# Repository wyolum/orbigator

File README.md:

# 🌍 Orbigator: The Analog Orbit Propagator

> "What hardware hacker doesn’t have a soft spot for transparent cases? ... [wyojustin] has done a fantastic job of documenting the hardware and software aspects of the build." — **[Hackaday](https://hackaday.com/2026/03/08/the-orbigator-satellite-tracking-with-style/)** ([Full Feature Archive](docs/HACKADAY_FEATURE.md))

**The Orbigator** is an open-source, physical satellite tracker that turns complex orbital mechanics into a desk-side companion. Powered by the **Raspberry Pi Pico 2** and precision **DYNAMIXEL servos**, it physically points to the ISS (or any satellite) in real-time with zero drift.

---

## 🚀 Why the Orbigator?

Inspired by [Will’s Builds ISS tracker](https://hackaday.com/2025/07/08/touch-lamp-tracks-iss-with-style/), the Orbigator introduces several key technical innovations to the DIY tracker space:

### 🔄 Continuous, Uninterrupted Motion
Unlike traditional trackers that use static globes (requiring wire unwinding every orbit), the Orbigator features a **rotating globe**. This allows for smooth, continuous tracking across multiple revolutions without ever needing to reset or "unwind."

### 🎯 LVLH Attitude Control
The orbital mechanics are implemented directly in the hardware geometry (inclination angle). This ensures the satellite pointer maintains a true **LVLH (Local Vertical, Local Horizontal)** attitude throughout the entire pass—exactly how real satellites orient themselves.

### 🧩 Zero-Drift absolute Positioning
Leveraging the 32-bit absolute resolvers in DYNAMIXEL XL330-M288-T motors, the system recovers its orientation instantly after power cycles. No homing, no limits, and no drift—just persistent, mathematical accuracy.

---

## 🛠️ Technical Deep Dive

*Complete Mechanical Assembly: Precision motion and integrated control.*

### Lightweight, High-Performance Propagator
The heart of the Orbigator is a custom, **lightweight SGP4 implementation** running natively on the Pico 2's RISC-V cores. Eschewing heavy ports, it was rolled specifically to provide mathematical accuracy within the visual tolerances of the physical hardware, handling real-time TLE propagation and J2 perturbation effects entirely in MicroPython.

### Split-Screen Radar UI
A custom **SH1106 OLED driver** provides a powerful command center:
*   **Live Radar Plot**: A dynamic "Sky Plot" of the current satellite pass.
*   **Localized World Map**: High-speed bitmask rendering provides a 90° ground track view centered on your observer location.

### Smart Persistence
The system monitors its own state and saves to Flash/SRAM only during ideal intervals (e.g., at equator crossings) to maximize flash lifespan while ensuring a perfect "instant-on" recovery.

---

## 📦 Repository Structure

| Path | Description |
|------|-------------|
| [**micropython/**](micropython/) | Firmware: SGP4 propagator, UI stacks, and motor drivers. |
| [**fabricate/**](fabricate/) | Mechanical design: OpenSCAD files for 3D printing and assembly. |
| [**kicad/**](kicad/) | Electronics: PCB designs and schematics. |
| [**web/**](micropython/web/) | Dashboard: Real-time control and configuration via web interface. |

---

## ⚡ Quick Start

1.  **3D Print**: High-quality production STLs are located in [**fabricate/stls/Production/**](fabricate/stls/Production/).
2.  **Assemble**: Follow our step-by-step [**Assembly Instructions**](docs/ASSEMBLY.md).
3.  **Flash MicroPython**: Install the Pico 2 firmware.
4.  **Upload Code**: Use Thonny or `mpremote` to copy the `micropython/` files to the board.
5.  **Track!**: Power up and select your satellite from the "SGP4" menu.

---

## 🧾 Bill of Materials (BOM)

### Electronics
*   **Controller**: [Raspberry Pi Pico 2W](https://www.adafruit.com/product/6087)
*   **Motors**: 2x [DYNAMIXEL XL330-M288-T](https://robotis.us/dynamixel-xl330-m288-t/)
*   **Display/UI**: [I2C OLED Display with EC11 Rotary Encoder](https://www.crcibernetica.com/i2c-oled-display-with-ec11-rotary-encoder/) (includes 2x buttons)
*   **RTC**: [DS3232 Precision RTC](https://www.dfrobot.com/product-2304.html)
*   **Logic**: 1x [SN74HC126N Quad Tri-State Buffer](https://www.digikey.com/en/products/detail/texas-instruments/SN74HC126N/376889) (for half-duplex UART)
*   **Passives**: 1x 10kΩ resistor, 2x 4.7kΩ resistors
*   **Power**: 5V 4-5A External Power Supply with [5.5mm DC Barrel Jack](https://www.amazon.com/dp/B0D9B7WR23)

### Hardware & Mechanical
*   **Globe**: [12" Transparent Desktop Globe](https://www.amazon.com/dp/B0086OHL9A)
*   **Bearings**: 3x [13mm OD Carbon Steel Ball Bearings](https://www.amazon.com/dp/B07SV6QSR3) (e.g., 624ZZ) and [High-Performance Skate Bearings](https://www.amazon.com/dp/B09MPMW1XQ)
*   **Fasteners**: Self-tapping screws (included with motors), [M3 Male Stud Mounting Magnets](https://www.kjmagnetics.com/mm-c-12-neodymium-male-stud-mounting-magnet?pl=1.2&pf=), and [Tension Springs](https://www.amazon.com/dp/B076LZ8L1M)
*   **Hardware**: 10-20 US pennies (used as counterweight)
*   **3D Parts**: Printed from the `Production/` folder (PLA or PETG)

---

## 📐 3D Printing (Production Parts)

The following parts are required for the full assembly and can be found in `fabricate/stls/Production/`. **The leading number in the filename indicates the required print quantity.**

*   `1_drive_gear.stl` - Main EQX drive
*   `1_flex_aov_arm.stl` - Satellite pointer arm
*   `1_globe_interface.stl` - Secure mount for the globe
*   `1_inclination_aov_mount.stl` - Hardware-implemented inclination bracket
*   `1_sled_3.stl` - Electronic housing and base
*   `1_full_assembly.stl` - Reference model (not for printing)
*   `3_swingarm.stl` - Differential assembly components
*   `3_shim.stl` - Insert for the skate bearings (see `misc.scad` for 13mm dims)
*   `3_washer.stl` - Vertical stop for the ring gear

---

## 📸 Media: As Seen on [WyoLum Blog](https://wyolum.com/orbigator-real-time-satellite-tracker-with-overhead-alert-radar/)

| [**Earthrise Shot**](docs/images/orbigator_lunar_display.jpg) | [**World Map Tracking**](docs/images/orbigator_worldmap_tracking.png) |
|:---:|:---:|
|  |  |
| *ISS Tracking with Lunar Projection.* | *Real-time World Map Context.* |

### System Details
| UI & Setup | Electronics | Mechanical Assembly | Technical Render |
|:---:|:---:|:---:|:---:|
|  |  |  |  |
| *Real-time status* | *Pico 2 & Buffers* | *Internal Hardware* | *Mathematical precision* |

> "A beautiful mix of technical precision and mechanical elegance."

---

## ⚖️ License

Distributed under the MIT License.

---

**Developed with ❤️ by wyojustin**
[GitHub](https://github.com/wyolum/orbigator)

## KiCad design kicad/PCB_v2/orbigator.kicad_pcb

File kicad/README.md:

# Orbigator KiCad Project

This directory contains the KiCad PCB design files for the Orbigator orbital mechanics simulator.

## Project Structure

```
kicad/
├── orbigator.kicad_pro      # KiCad 8.x project file
├── orbigator.kicad_sch      # Main schematic file
├── orbigator.kicad_pcb      # PCB layout file
├── sym-lib-table            # Symbol library table
├── fp-lib-table             # Footprint library table
├── orbigator.pretty/        # Custom footprints
├── bom/                     # Bill of Materials exports
├── gerber/                  # Gerber files for manufacturing
├── pdf/                     # PDF exports of schematics
├── renders/                 # PCB renders
├── 3D_models/               # Custom 3D models
└── orbigator-backups/       # Automatic backups
```

## Quick Start

1. Open `orbigator.kicad_pro` in KiCad 8.x
2. Review the schematic in the Schematic Editor
3. Use the reference documentation in the parent directory:
   - `ORBIGATOR_CIRCUIT_DIAGRAM.txt` - ASCII circuit diagram
   - `ORBIGATOR_PIN_ASSIGNMENTS.txt` - Pin assignments
   - `NOTE_FOR_ANOOL_I2C_PULLUPS.txt` - Critical design notes
   - `BOM.md` - Detailed component specifications

## Key Design Requirements

### Critical Components
- **I2C Pull-ups**: 4.7kΩ resistors on SDA and SCL (REQUIRED for multi-device bus)
- **RTC Backup**: 0.47F supercapacitor with 47Ω charging resistor (recommended)
- **DATA Bus Pull-up**: 10kΩ resistor to +5V for DYNAMIXEL communication

> **Note for Anool**: For the RTC (DS3231), you can choose between:
> 1. Using a ChronoDot module breakout (simple pinout connection)
> 2. Integrating the DS3231 chip directly with battery backup (CR2032)
> 3. Integrating the DS3231 chip directly with supercapacitor backup (0.47F)
> 
> The choice is yours based on board space, cost, and maintenance preferences.

### Power Requirements
- **3.3V Rail**: Pico 2, 74HC126, OLED, RTC (low current)
- **5V Rail**: DYNAMIXEL motors (4-5A external supply required)

### Connectors
- **DYNAMIXEL**: 3-pin JST connectors (daisy-chained)
- **Encoder**: 5-pin header (A, B, SW, VCC, GND)
- **Power**: Barrel jack or terminal block for 5V input

## Design Notes

This PCB is designed to be a single-board controller for the Orbigator display.
All components should be easily hand-solderable (through-hole or large SMD).

The design prioritizes:
- Reliability (proper pull-ups, decoupling)
- Serviceability (labeled connectors, test points)
- Compactness (suitable for display base mounting)

## Manufacturing

Standard 2-layer PCB:
- Thickness: 1.6mm
- Copper: 1oz
- Finish: HASL or ENIG
- Minimum trace: 0.2mm
- Minimum clearance: 0.2mm

## Author

Design by Anool Mahidharia (WyoLum)
Based on specifications by Justin Shaw

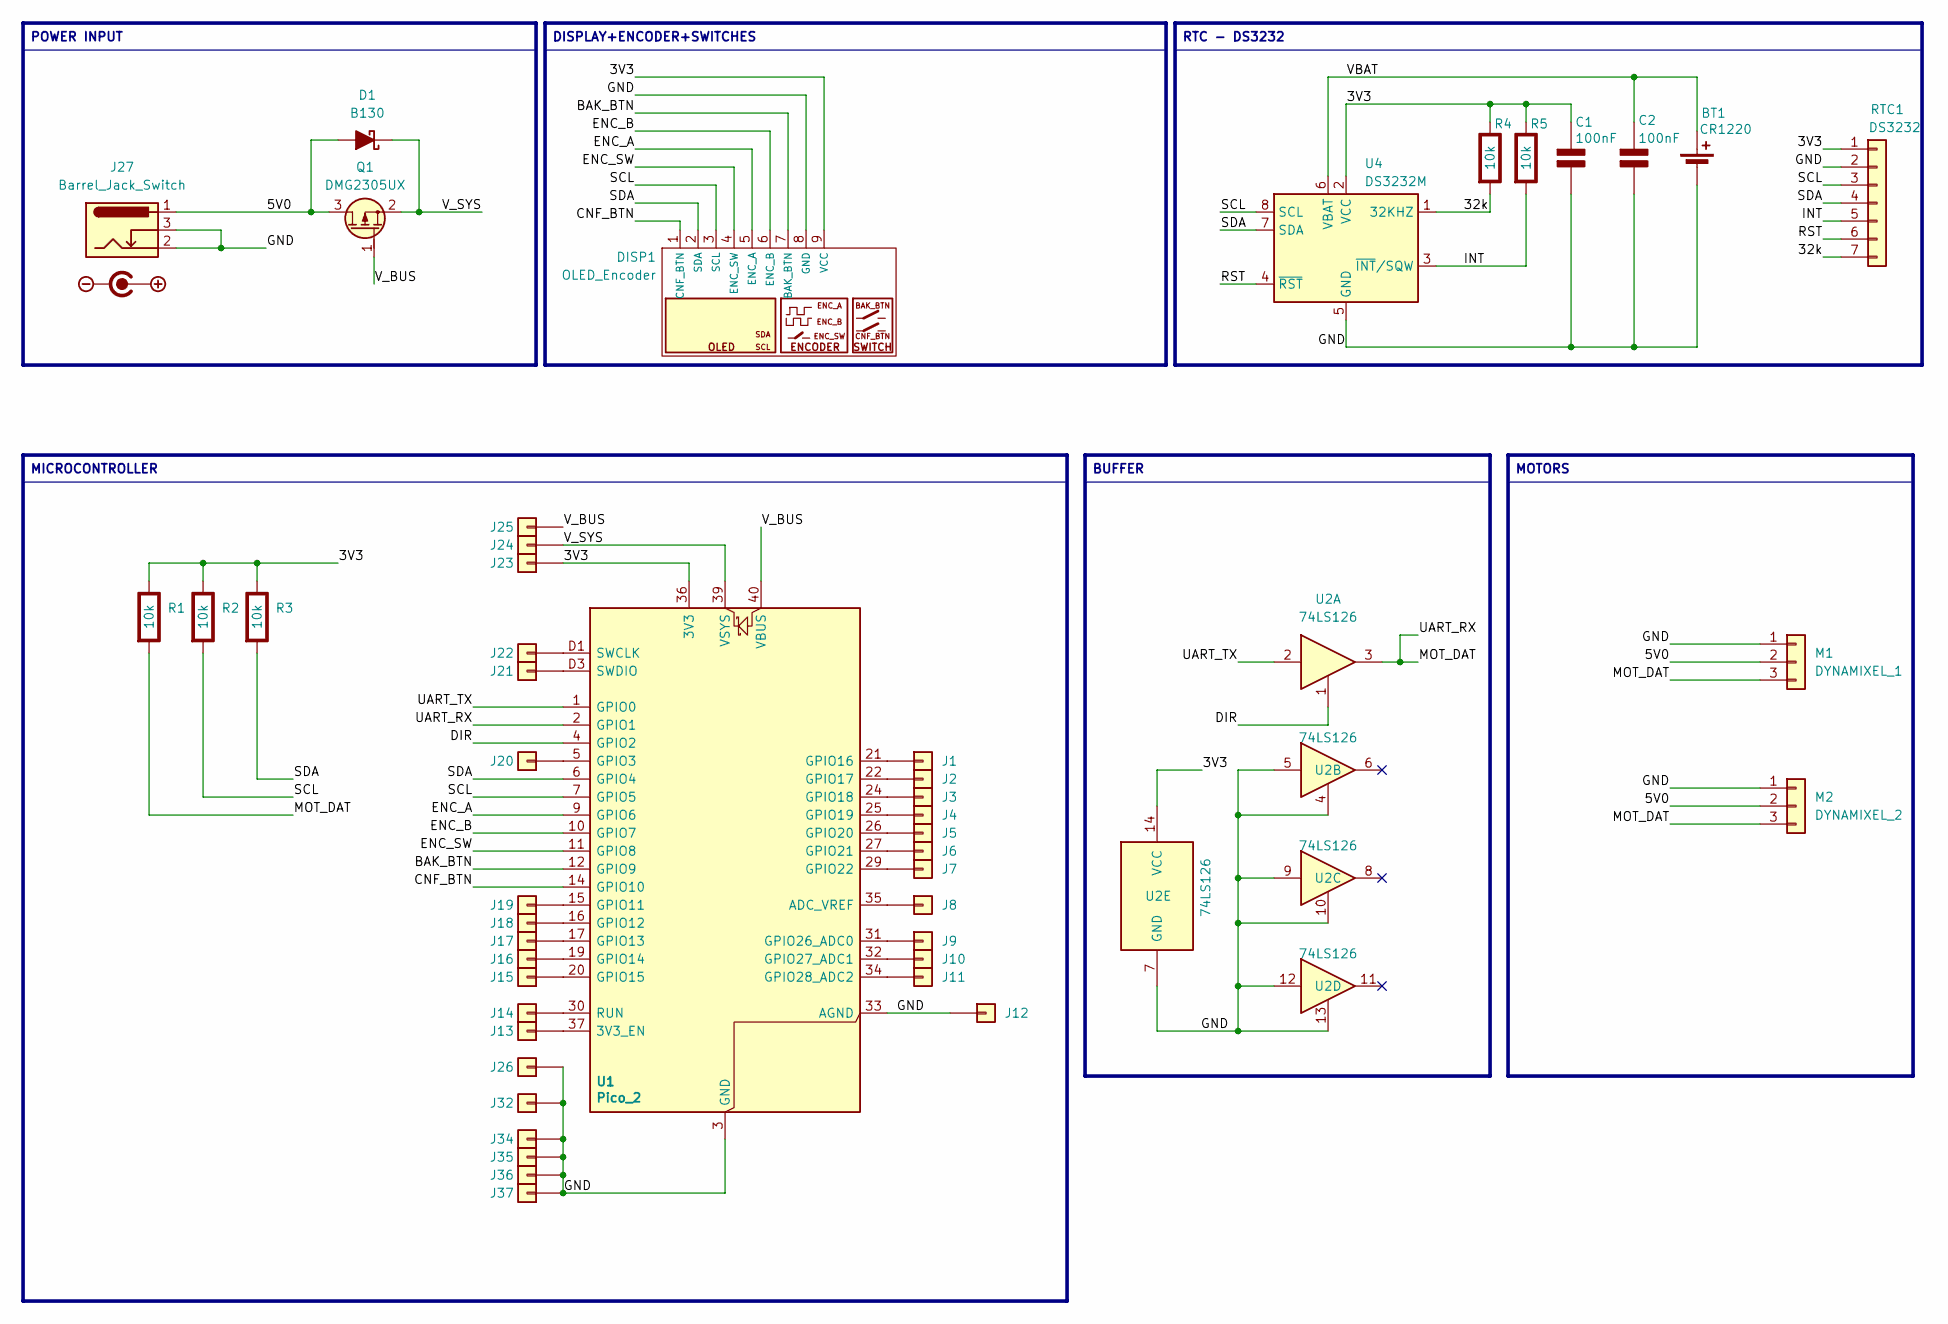
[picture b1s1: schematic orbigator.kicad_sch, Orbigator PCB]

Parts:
BT1: CR1220; BatteryHolder_LINX_BAT-HLD-012-SMT
C1, C2: 100nF; C_0805_2012Metric_Pad1.18x1.45mm_HandSolder; Rating V
D1: B130; D_SMA
DISP1: OLED_Encoder; OLED_ENC3
J1, J2, J3, J4, J5, J6, J7, J8, J9, J10, J11, J12, J13, J14, J15, J16, J17, J18, J19, J20, J21, J22, J23, J24, J25, J26, J32, J34, J35, J36, J37: Conn_01x01; PinHeader_1x01_P2.54mm_Vertical
J27: Barrel_Jack_Switch; BarrelJack_Horizontal
M1: DYNAMIXEL_1; JST_EH_B3B-EH-A_1x03_P2.50mm_Vertical
M2: DYNAMIXEL_2; JST_EH_B3B-EH-A_1x03_P2.50mm_Vertical
Q1: DMG2305UX; SOT-23
R1, R2, R3, R4, R5: 10k; R_0805_2012Metric_Pad1.20x1.40mm_HandSolder; Rating W
RTC1: DS3232; DS3232_RTC_vert
U1: Pico_2; RaspberryPi_Pico_SMD_HandSolder
U2: 74LS126; SOIC-14_3.9x8.7mm_P1.27mm
U3: DC_polarity; DC
U4: DS3232M; SOIC-8_3.9x4.9mm_P1.27mm

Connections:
/3V3: C1.1 (+), DISP1.9 (VCC), J23.1, R1.1 (+), R2.1 (+), R3.1 (+), R4.1 (+), R5.1 (+), RTC1.1, U1.36 (3V3), U2.14 (VCC), U4.2 (VCC)
/5V0: D1.2 (A), J27.1, M1.2, M2.2, Q1.3 (D)
/32k: R4.2 (-), RTC1.7, U4.1 (32KHZ)
/BAK_BTN: DISP1.7 (BAK_BTN), U1.12 (GPIO9)
/CNF_BTN: DISP1.1 (CNF_BTN), U1.14 (GPIO10)
/DIR: U1.4 (GPIO2), U2.1
/ENC_A: DISP1.5 (ENC_A), U1.9 (GPIO6)
/ENC_B: DISP1.6 (ENC_B), U1.10 (GPIO7)
/ENC_SW: DISP1.4 (ENC_SW), U1.11 (GPIO8)
/GND: BT1.2 (-), C1.2 (-), C2.2 (-), DISP1.8 (GND), J12.1, J26.1, J27.2, J27.3, J32.1, J34.1, J35.1, J36.1, J37.1, M1.1, M2.1, RTC1.2, U1.3 (GND), U1.8 (GND), U1.13 (GND), U1.18 (GND), U1.23 (GND), U1.28 (GND), U1.33 (AGND), U1.38 (GND), U1.D2 (GND), U2.4, U2.5, U2.7 (GND), U2.9, U2.10, U2.12, U2.13, U4.5 (GND)
/INT: R5.2 (-), RTC1.5, U4.3 (~INT/SQW)
/MOT_DAT: M1.3, M2.3, R1.2 (-), U1.2 (GPIO1), U2.3
/RST: RTC1.6, U4.4 (~RST)
/SCL: DISP1.3 (SCL), R2.2 (-), RTC1.3, U1.7 (GPIO5), U4.8 (SCL)
/SDA: DISP1.2 (SDA), R3.2 (-), RTC1.4, U1.6 (GPIO4), U4.7 (SDA)
/UART_TX: U1.1 (GPIO0), U2.2
/VBAT: BT1.1 (+), C2.1 (+), U4.6 (VBAT)
/V_BUS: J25.1, Q1.1 (G), U1.40 (VBUS)
/V_SYS: D1.1 (K), J24.1, Q1.2 (S), U1.39 (VSYS)
unnamed: J1.1, U1.21 (GPIO16)
unnamed: J2.1, U1.22 (GPIO17)
unnamed: J3.1, U1.24 (GPIO18)
unnamed: J4.1, U1.25 (GPIO19)
unnamed: J5.1, U1.26 (GPIO20)
unnamed: J6.1, U1.27 (GPIO21)
unnamed: J7.1, U1.29 (GPIO22)
unnamed: J8.1, U1.35 (ADC_VREF)
unnamed: J9.1, U1.31 (GPIO26_ADC0)
unnamed: J10.1, U1.32 (GPIO27_ADC1)
unnamed: J11.1, U1.34 (GPIO28_ADC2)
unnamed: J13.1, U1.37 (3V3_EN)
unnamed: J14.1, U1.30 (RUN)
unnamed: J15.1, U1.20 (GPIO15)
unnamed: J16.1, U1.19 (GPIO14)
unnamed: J17.1, U1.17 (GPIO13)
unnamed: J18.1, U1.16 (GPIO12)
unnamed: J19.1, U1.15 (GPIO11)
unnamed: J20.1, U1.5 (GPIO3)
unnamed: J21.1, U1.D3 (SWDIO)
unnamed: J22.1, U1.D1 (SWCLK)

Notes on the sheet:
DISPLAY+ENCODER+SWITCHES
POWER INPUT
MOTORS
RTC - DS3232
BUFFER
MICROCONTROLLER

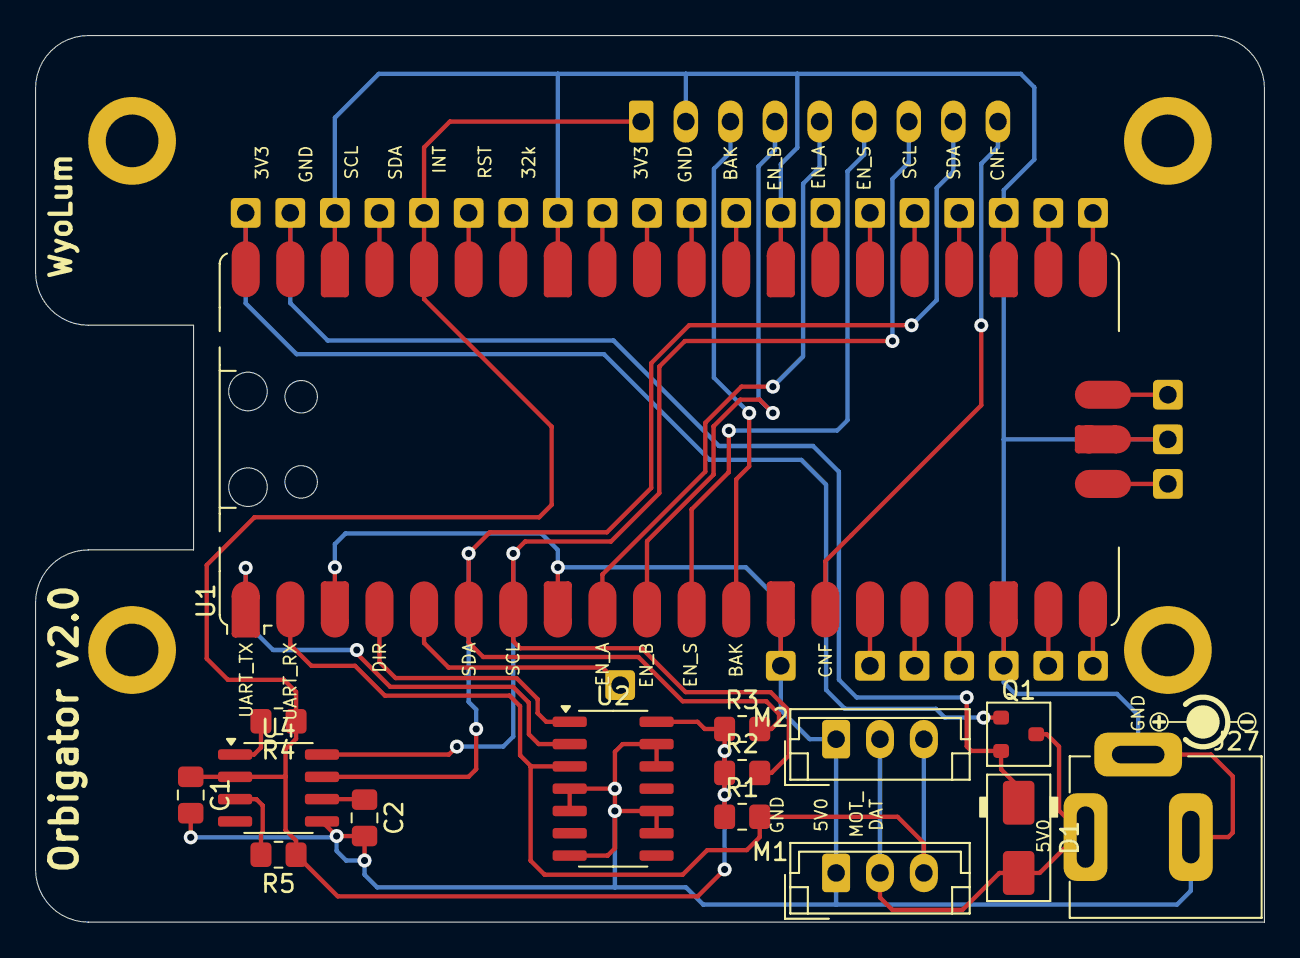
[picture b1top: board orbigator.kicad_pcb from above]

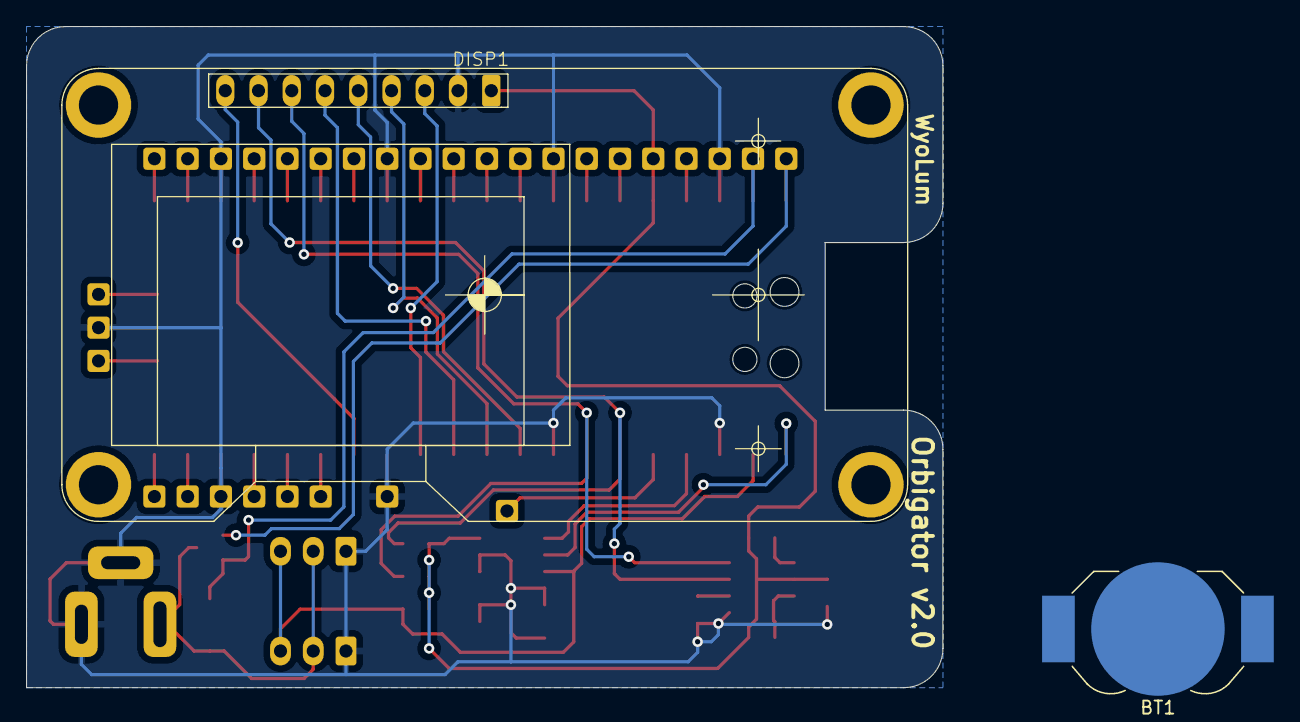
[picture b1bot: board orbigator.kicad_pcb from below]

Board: 2 copper layers, 70.0 x 50.5 mm, 49 parts (2 on the bottom side), 39 nets.

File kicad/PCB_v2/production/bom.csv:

Designator,Footprint,Quantity,Value,LCSC Part #,JLCPCB Part #,LINK
BT1,BatteryHolder_LINX_BAT-HLD-012-SMT,1,CR1220,C381116,,
"C1, C2",805,2,100nF,C49678,,https://www.lcsc.com/product-detail/C49678.html?s_z=n_CC0805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
D1,D_SMA,1,B130,C134423,,https://www.lcsc.com/product-detail/C134423.html?s_z=n_B130-13-F
DISP1,OLED_ENC3,1,OLED_Encoder,,,
J27,BarrelJack_Horizontal,1,Barrel_Jack_Switch,C381116,,https://www.lcsc.com/product-detail/C381116.html
M1,JST_EH_B3B-EH-A_1x03_P2.50mm_Vertical,1,DYNAMIXEL_1,C160259,,https://www.lcsc.com/product-detail/C160259.html?s_z=n_JST_E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
M2,JST_EH_B3B-EH-A_1x03_P2.50mm_Vertical,1,DYNAMIXEL_2,C160259,,https://www.lcsc.com/product-detail/C160259.html?s_z=n_JST_E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
Q1,SOT-23,1,DMG2305UX,C150470,,https://www.lcsc.com/product-detail/C150470.html?s_z=n_DMG2305UX
"R1, R2, R3, R4, R5",805,5,10k,C84376,,https://www.lcsc.com/product-detail/C84376.html
U1,RaspberryPi_Pico_SMD_HandSolder,1,Pico_2,,C41407547,https://jlcpcb.com/partdetail/RaspberryPi-Pico2/C41407547
U2,SOIC-14_3.9x8.7mm_P1.27mm,1,74LS126,C7644,,https://www.lcsc.com/product-detail/C7644.html?s_z=n_SN74HC126DR
U4,SOIC-8_3.9x4.9mm_P1.27mm,1,DS3232M,C2827535,,https://www.lcsc.com/product-detail/C2827535.html?s_z=n_DS3232M

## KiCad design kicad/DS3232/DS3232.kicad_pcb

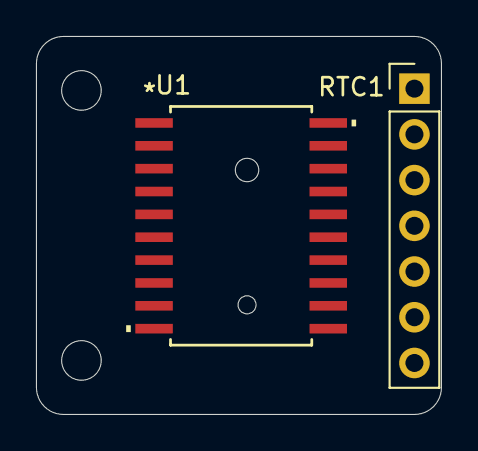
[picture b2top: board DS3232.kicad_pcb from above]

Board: 2 copper layers, 22.5 x 21.0 mm, 5 parts (1 on the bottom side), 7 nets, no tracks yet.

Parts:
BT1: CR1220; BAT_1056
H1, H2: MountingHole; MountingHole_2.2mm_M2
RTC1: DS3232; PinHeader_1x07_P2.54mm_Vertical
U1: ds3232sn-; 21-0042B_20_MXM-M

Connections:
/3V3: RTC1.1, U1.4 (VCC)
/32k: RTC1.7, U1.3 (32KHZ)
/GND: RTC1.2, U1.15 (GND)
/INT: RTC1.5, U1.5 (*INT/SQW)
/RST: RTC1.6, U1.6 (*RST)
/SCL: RTC1.3, U1.18 (SCL), U1.20 (SCL)
/SDA: RTC1.4, U1.17 (SDA)

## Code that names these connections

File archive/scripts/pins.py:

# pins.py - Orbigator GPIO Assignment Module
# Raspberry Pi Pico 2 with DYNAMIXEL XL330-M288-T Motors
# Aligned with orbigator.py and ORBIGATOR_PIN_ASSIGNMENTS.txt

from machine import Pin

# ---------------------------
# DYNAMIXEL Communication (UART0 + 74HC126 Buffer)
# ---------------------------
UART_TX = 0      # GP0 - UART0 TX → 74HC126 Pin 2 (1A)
UART_RX = 1      # GP1 - UART0 RX → DYNAMIXEL DATA line
UART_DIR = 2     # GP2 - Direction Control → 74HC126 Pin 1 (1OE)

# ---------------------------
# I2C Bus (OLED + DS3231 RTC)
# ---------------------------
I2C_SDA = 4      # GP4 - I2C0 SDA (shared: OLED + RTC)
I2C_SCL = 5      # GP5 - I2C0 SCL (shared: OLED + RTC)

# ---------------------------
# Rotary Encoder
# ---------------------------
ENC_A = 6        # GP6 - Encoder Phase A (with internal pull-up)
ENC_B = 7        # GP7 - Encoder Phase B (with internal pull-up)
ENC_SW = 8       # GP8 - Encoder Switch (with internal pull-up)

# ---------------------------
# Helper Pin Constructors
# ---------------------------
# UART pins (managed by UART peripheral, typically not constructed manually)
uart_dir_pin = Pin(UART_DIR, Pin.OUT)

# I2C pins (managed by I2C peripheral)
# i2c_sda_pin = Pin(I2C_SDA, Pin.OUT, Pin.OPEN_DRAIN)
# i2c_scl_pin = Pin(I2C_SCL, Pin.OUT, Pin.OPEN_DRAIN)

# Encoder pins
enc_a_pin = Pin(ENC_A, Pin.IN, Pin.PULL_UP)
enc_b_pin = Pin(ENC_B, Pin.IN, Pin.PULL_UP)
enc_sw_pin = Pin(ENC_SW, Pin.IN, Pin.PULL_UP)

# ---------------------------
# Motor Configuration
# ---------------------------
# DYNAMIXEL Motor IDs
MOTOR_ID_AOV = 1  # Argument of Vehicle (direct drive)
MOTOR_ID_EQX = 2  # Equator crossing (11T → 120T gearing)

# Gear Ratios
EQX_GEAR_RATIO = 120.0 / 11.0  # Ring gear / Drive gear
AOV_GEAR_RATIO = 1.0            # Direct drive

# ---------------------------
# UART Configuration
# ---------------------------
UART_BAUD = 57600
UART_BITS = 8
UART_PARITY = None
UART_STOP = 1

# ---------------------------
# I2C Configuration
# ---------------------------
I2C_FREQ = 100_000  # 100 kHz for reliability with ChronoDot/DS3231

# I2C Addresses
OLED_ADDR = 0x3C    # OLED Display (SH1106/SSD1306)
RTC_ADDR = 0x68     # DS3231 RTC (ChronoDot)

# ---------------------------
# Encoder Configuration
# ---------------------------
DETENT_DIV = 2      # Encoder counts per detent (for responsiveness)
DEBOUNCE_MS = 200   # Button debounce time in milliseconds

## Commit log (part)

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2025-07-25 initial
2025-07-28 reshuffle
2025-07-28 added screenshots
2025-07-28 added README
2025-11-17 scad work
2025-11-23 Add FreeCAD script to batch convert STL files to STEP format
    Creates step_files/ directory and converts all STL files from
    fabricate/ and fabricate/stls/ to STEP format using FreeCAD's
    mesh-to-solid conversion.
2025-11-23 added a list of stls to skip
2025-11-23 Switch to environment variables for FreeCAD script args
    FreeCAD intercepts command line arguments before they reach the script,
    so use STL_MODE and STL_FILES environment variables instead.
2025-11-23 Simplify STL-to-STEP script to just use skip list
    Removed environment variable complexity - just converts all STL files
    except those in SKIP_LIST.
2025-11-23 Add launch script for STL-to-STEP conversion
2025-11-23 Update render_aov_arm with full assembly transformation
2025-11-23 Add in-situ rendering for all assembly components
    - render_in_situ.scad: Master file with all component transformations
    - render_all_in_situ.sh: Batch script to render all components
    - stls_in_situ/: Output directory for positioned STL files
    Components include: aov_arm, aov_motor_mount, sled, ring_gear,
    drive_gear, base_with_1010_hole, RingLock, idler, spring_arms, pico
2025-11-23 Update render_aov_arm to use 'use' instead of 'include'
2025-11-23 Add render file for base_with_1010_hole in assembly position
2025-11-23 Add render file for 1010 aluminum extrusion in assembly position
2025-11-23 added in_situ step files
2025-11-30 updated files
2025-11-30 Update AOV motor to move ~0.5 degrees per encoder click
    - Set AOV_STEPS_PER_DETENT to 6 half-steps (~0.527 degrees)
    - Keep LAN_STEPS_PER_DETENT at 1 step
    - Update display to show AOV position in degrees instead of revolutions
    - More intuitive feedback for the highly-geared AOV motor
2025-12-01 Fix DS3231 I2C communication reliability
    - Switch from readfrom_mem to write-then-read method (more reliable)
    - Lower I2C frequency to 100kHz for better ChronoDot compatibility
    - Update both datetime() and temperature() methods
    - Fixes EIO error when reading from DS3231 registers
2025-12-02 Add long press time setting with DS3231 RTC integration
    - Long press (1s) encoder button enters time-setting mode
    - Short press cycles through states or time fields
    - Encoder adjusts hour/minute/year/month/day fields
    - Blinking cursor shows active field
    - Saves to DS3231 RTC on long press exit
    - Lower I2C frequency to 100kHz for RTC compatibility
2025-12-02 fix: Use str() wrapper for RTC exception to avoid printing errors
2025-12-02 fix: Add missing import time to ds3231.py and clean up debug statements
    - ds3231.py was missing 'import time' causing NameError during RTC init
    - Removed debug print statements from orbigator.py RTC initialization
    - RTC now initializes correctly with ChronoDot/DS3231 hardware
2025-12-07 Add DYNAMIXEL documentation and setup files
2025-12-07 Update documentation for XC330-M288-T servo selection
    XL330-M288-T backordered until Q1 2026. Selected XC330-M288-T as
    upgraded alternative with:
    - Metal gears (vs plastic)
    - Upgraded bearings
    - 78% more torque
    - Immediate availability
2025-12-16 Add DYNAMIXEL dry lab setup guide with official pinout diagram
    - Comprehensive step-by-step setup guide for XL330 motors
    - Pin identification guide showing mirrored connectors
    - Official ROBOTIS pinout diagram
    - Screw depth safety calculations
    - Drive shaft adapter with named parameters
2025-12-18 Orbigator Dynamixel Rewrite - Complete Implementation
    Major Changes:
    - Rewrote orbigator.py to use DYNAMIXEL XL330-M288-T motors (745 lines, down from 800)
    - Created motor abstraction layer (dynamixel_motor.py) with gear ratio support
    - Motor ID assignments: ID 1 = AoV (direct), ID 2 = LAN (10.909:1 geared)
    - Removed all stepper motor code (~400 lines)
    - Simplified motion control (motors handle acceleration internally)
2025-12-20 Fix motor control and I2C issues, add documentation
    Major fixes:
    - Add I2C pull-up resistors (4.7kΩ on SDA/SCL) to fix display glitching
    - Implement get_new_pos() for Extended Position Mode wrapping
    - Fix motor rate initialization bug when starting in state 3
    - Fix catch-up mechanism to prevent extreme motor movements
    - Reduce display update to 1Hz for better I2C performance
2025-12-21 Add KiCad PCB outline with centered mounting holes
    - Created orbigator.kicad_pcb with 55x70mm board outline
    - Board rotated 90° and centered on A4 sheet
    - Added 4x M3 mounting holes matching display board pattern
    - Holes positioned at (75.5,134), (75.5,163), (134.5,134), (134.5,163)
    - Hole pattern centered on board to align with display board
    - Added silkscreen text: 'Orbigator v1.0' and 'WyoLum'
2025-12-25 Add back/confirm buttons (GP9/GP10) and fix EQX motor direction
    - Added GP9 (Back button) and GP10 (Confirm button) to pin assignments
    - Updated component list to include new buttons
    - Fixed EQX motor direction (negated rate) - sun now rises in east
    - Added test_buttons.py for button verification
    - All buttons tested and working
2025-12-25 Implement revolution-based persistence, shortest-path catch-up logic, and hardware safety limits. Update README.
2025-12-25 Update all READMEs to reflect final Dynamixel/Mode-based features including Zulu time and inclination control.
2025-12-25 Add links to key documentation files in README.
2025-12-25 Added DYNAMIXEL XL-330 connector specifications document.
2025-12-25 Fixed dead DigiKey links for JST-GH housings and crimp contacts.
2025-12-25 Corrected JST-GH PCB header links in documentation.
2025-12-25 Updated PCB header links with cleaner Mouser URLs.
2025-12-25 Added Zulu Time (Datetime) editor and boot-time RTC reset check to prompt for time if reset.
2025-12-25 Updated upload script to include modes.py, orb_globals.py, and orb_utils.py.
2025-12-25 Promoted manual motor alignment to the main menu and verified encoder inversion.
2025-12-25 Added pro-tip about perfect stock cable lengths.
2025-12-25 Fixed AoV drift by implementing high-resolution system time syncing and high-precision catch-up anchors.
2025-12-25 Fixed Orbit re-entry drift by anchoring catch-up to current motor position relative to elapsed time.
2025-12-25 Reverted AoV speed limit to 10.
2025-12-25 Refactor: Introduced pins.py and addressed code review feedback.
2025-12-25 Added fine/coarse adjustment toggle to MotorEditorMode (encoder press switches between 1.0 and 0.1 degree steps)
2025-12-25 Implemented robustness improvements: centralized encoder policy and DYNAMIXEL communication resilience with retry logic and degraded mode
2025-12-25 Implemented elliptical orbit support with Kepler's equation solver, variable velocity integration, and UI editors for eccentricity and periapsis
2025-12-25 Added Plan13 satellite propagator and TLE utilities (adapted from bkerler/sattracker), created thank you note for bkerler
2025-12-25 Updated Plan13 test with current ISS TLE (TLE parsing still WIP)
2025-12-25 Added distance variation comparison over one orbit - ISS range varies by 729km (7.8%) from observer location
2025-12-25 Updated Plan13 GHAA for 2025 but still has 9400km longitude error - Plan13 unsuitable, need SGP4
2025-12-26 Discovered and validated existing SGP4 implementation - ready for satellite tracking integration
2025-12-28 Optimize performance, implement live motor tuning, and add incremental sync scripts
2025-12-28 SRAM state: add version byte + checksum validation
2025-12-30 SRAM state: integrate boot logging
2025-12-30 Mechanical: increase globe_interface_ring scale to 1.02 for better fit
2025-12-30 UI: universal accelerated encoder for all parameter editors
2025-12-30 UI: graphical degree symbol for OLED
2025-12-30 Docs: update Status Report for ChatGPT sharing
2025-12-30 Docs: finalize motor longevity wording for ChatGPT sharing
2026-01-03 Enable motors on hardware: Force torque ON and increase speed limit
2026-01-03 Fix SGP4 mapping: EQX formula and 2-digit year handling
2026-01-03 docs: add blog update and images
2026-01-04 KiCad schematic WiP
2026-01-07 Fix Motor Speed, SRAM Persistence, TrackLLMode, and Repo Cleanup
2026-01-07 Update gores: Full width tabs
2026-01-10 simple iss model added
2026-01-11 PCB check parts placement
2026-01-12 PCB modified RTC layout
2026-01-17 PCB layout please verify
2026-01-31 v2 DISP_ENC flip corrected in PCB
2026-02-01 Clean up backup and temp files
2026-02-02 v2 Motor connectors flip 180 deg in PCB
2026-02-08 WIP: Save current state before TDD rewrite
2026-02-18 feat: Final Polish - TLE Updates, Homing Fix, Stiction Tuning, Splash Screen
    - TLE Updates: 12h cycle with background check
    - Homing: AoV -> 90° Zenith, Nearest Logic
    - Tuning: AoV PID P=1000/I=50 to fix stiction
    - UX: Splash Screen with countdown + sh1106 refactor
    - Safety: 5s boot delay
    - Refactor: Shared sh1106 driver
2026-02-22 feat: Overhead Alert Radar (feature/overhead-alert-radar)
    - observer_frame.py: ECEF station + trig-free dot_up + az_el_deg
    - overhead_watcher.py: hysteresis state machine (HORIZON_ON=0)
    - radar_display.py: sky plot with trail ring buffer, 128x64
    - propagate.py: expose last_ecef from MicroSGP4
    - orb_globals.py: observer_frame, overhead_watcher, radar_display vars
    - orb_utils.py: fetch_observer_location() via Wyolum endpoint
2026-02-23 fix: trail 1pt/min, 20-pt buffer (covers full pass to set)
2026-02-23 feat: radar right-half layout, fast-forward test
    - radar_display: radar on right half (CX=96 R=29), Az/El on left
    - test: scan real TLE for next pass, animate actual track
2026-02-25 fix: DS3231 → DS3232 in live docs
2026-02-28 added production STLs
2026-03-02 Implement manual Lat/Lon editor and refactor overhead alert init
2026-03-02 fix: LatLonEditorMode arm logic — inline imports, drop redundant input_utils import
    Importing from orbigator.py would re-execute all module-level init code
    (motors, WiFi, etc.). Inline the three observer imports directly instead.
    Also remove the redundant local `import input_utils` since it is already
    imported at the top of modes.py.
    https://claude.ai/code/session_014H7TD89FRnXuv4wc5PGTdz
2026-03-08 Update README with Hackaday highlight and technical differentiators
2026-03-08 Detail 3D print quantities and mechanical roles in README
2026-03-08 Highlight main blog photos in README
2026-03-08 Fix README gallery formatting
2026-03-08 Update BOM with purchase links
2026-03-08 Update BOM with DS3232 and buffer links
2026-03-09 Add Hackaday quote to README
2026-03-09 Remove fake Hackaday.io link and fix accidental backticks
2026-03-09 Archive Hackaday feature and add display encoder layout
2026-03-10 Restore BOM components and clarify UI button inclusion
2026-03-11 Simplify Hackaday feature archive: remove community discussion
2026-03-22 orbigator v2 pcb ready for fab
2026-03-24 feat: add JLCPCB-format BOM for PCB v2
    Based on BOM.md v2.0 (supercap/bypass caps removed, CR2032 battery used).
    Includes LCSC part numbers for sourceable components, sourcing notes for
    modules ordered separately (Pico 2, OLED, RTC, DYNAMIXEL), and flags the
    SOIC-14 substitute for the DIP-14 74HC126 per the V2 SMD migration checklist.
    https://claude.ai/code/session_014H7TD89FRnXuv4wc5PGTdz
2026-03-26 orbigator v2 WIP2 - not final yet
2026-03-28 correct csv formatting for bom

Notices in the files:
README.md:
License: MIT
